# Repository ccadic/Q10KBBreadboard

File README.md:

# Q10KBBreadboard
Q10KB and OLED 0,96" display

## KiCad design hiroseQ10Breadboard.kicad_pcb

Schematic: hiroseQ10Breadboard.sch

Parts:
C1: 0.1uF; C_1206_HandSoldering
J1: COL_CON; Socket_Strip_Straight_1x10_Pitch2.54mm
J2: ROW_CON; Socket_Strip_Straight_1x09_Pitch2.54mm
LCD1: Oled96
Q1: BSS138; SOT-23
R1: 10k; R_1206_HandSoldering
R2: 1k; R_1206_HandSoldering
R3: 330; R_1206_HandSoldering
R4: 620; R_1206_HandSoldering
R5: 3.3k; R_1206_HandSoldering
R6: 2k; R_1206_HandSoldering
SW1: 5W_SW; 5WAY_sw
U1: Keyboard:BBQ10KBD; Q10KeyBoard2018

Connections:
/3.3v: C1.1, J1.8, LCD1.3 (Vcc), R6.1, U1.2, U1.24, U1.26
/Analog: J1.10, R6.2, SW1.5
/KB_COL1: J1.1, U1.7
/KB_COL2: J1.2, U1.9
/KB_COL3: J1.3, U1.10
/KB_COL4: J1.4, U1.17
/KB_COL5: J1.5, U1.19
/KB_LGHT: J1.7, Q1.1 (G), R1.1
/KB_MIC: J1.6, U1.3
/KB_ROW1: J2.1, U1.6
/KB_ROW2: J2.2, U1.8
/KB_ROW3: J2.3, U1.18
/KB_ROW4: J2.4, U1.20
/KB_ROW5: J2.5, U1.21
/KB_ROW6: J2.6, U1.22
/KB_ROW7: J2.7, U1.27
/SCL: J2.8, LCD1.2 (SCL)
/SDA: J2.9, LCD1.1 (SDA)
GND: C1.2, J1.9, LCD1.4 (GND), Q1.2 (S), R1.2, R2.2, R3.2, R4.2, R5.2, SW1.1, U1.1, U1.4, U1.5, U1.11, U1.12, U1.13, U1.14, U1.15, U1.16, U1.28
unnamed: Q1.3 (D), U1.23, U1.25
unnamed: R2.1, SW1.4
unnamed: R3.1, SW1.2
unnamed: R4.1, SW1.3
unnamed: R5.1, SW1.6

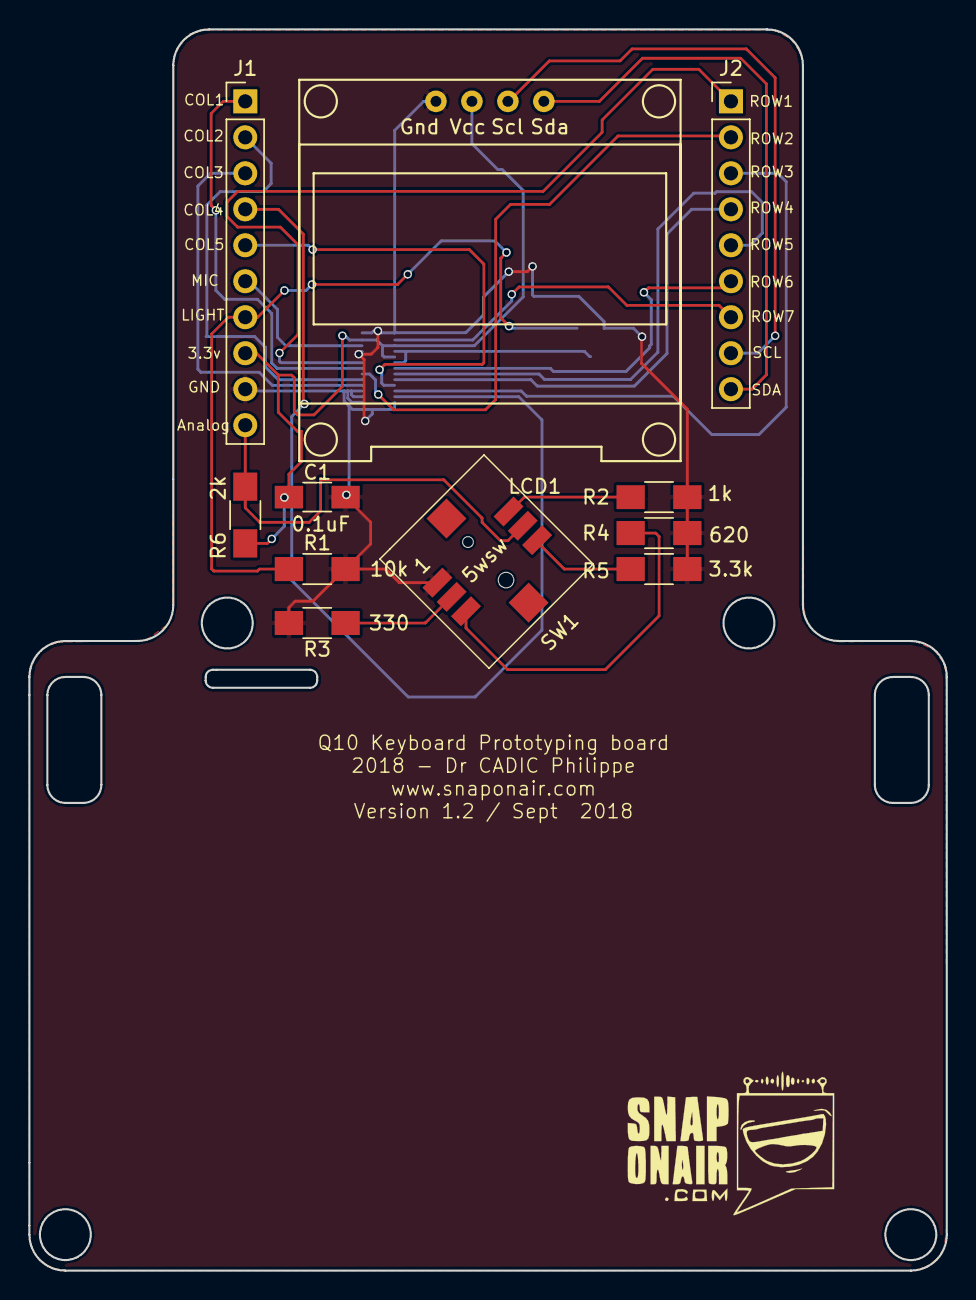
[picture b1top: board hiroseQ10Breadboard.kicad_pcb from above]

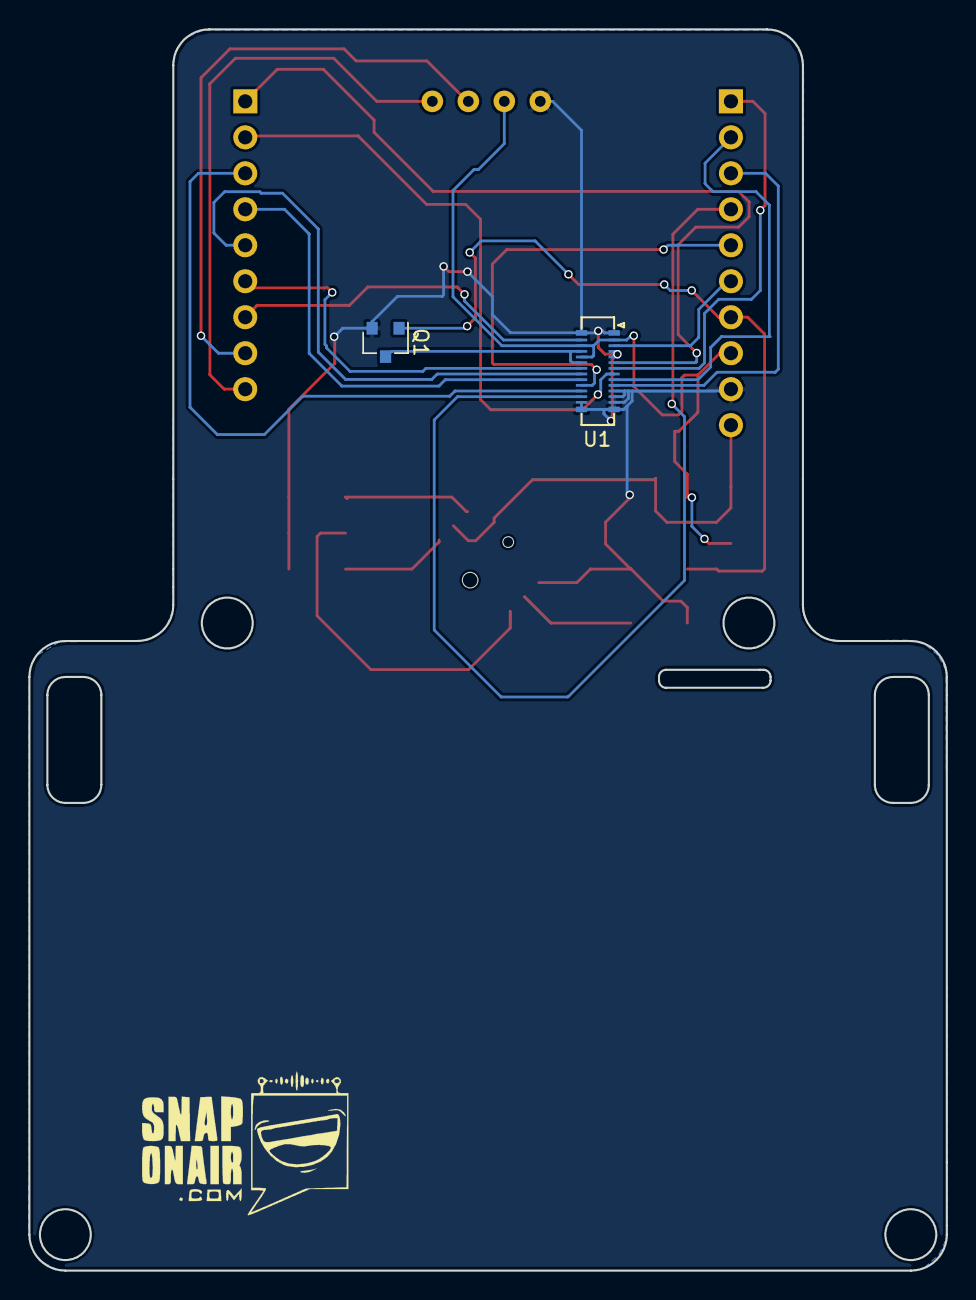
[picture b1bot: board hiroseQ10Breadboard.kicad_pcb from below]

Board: 2 copper layers, 64.8 x 87.6 mm, 13 parts (2 on the bottom side), 24 nets.
